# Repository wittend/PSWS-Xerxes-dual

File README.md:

# PSWS-Xerxes-dual
An SDR dual using ADC2808 converters and an FX-3 USB3 interface

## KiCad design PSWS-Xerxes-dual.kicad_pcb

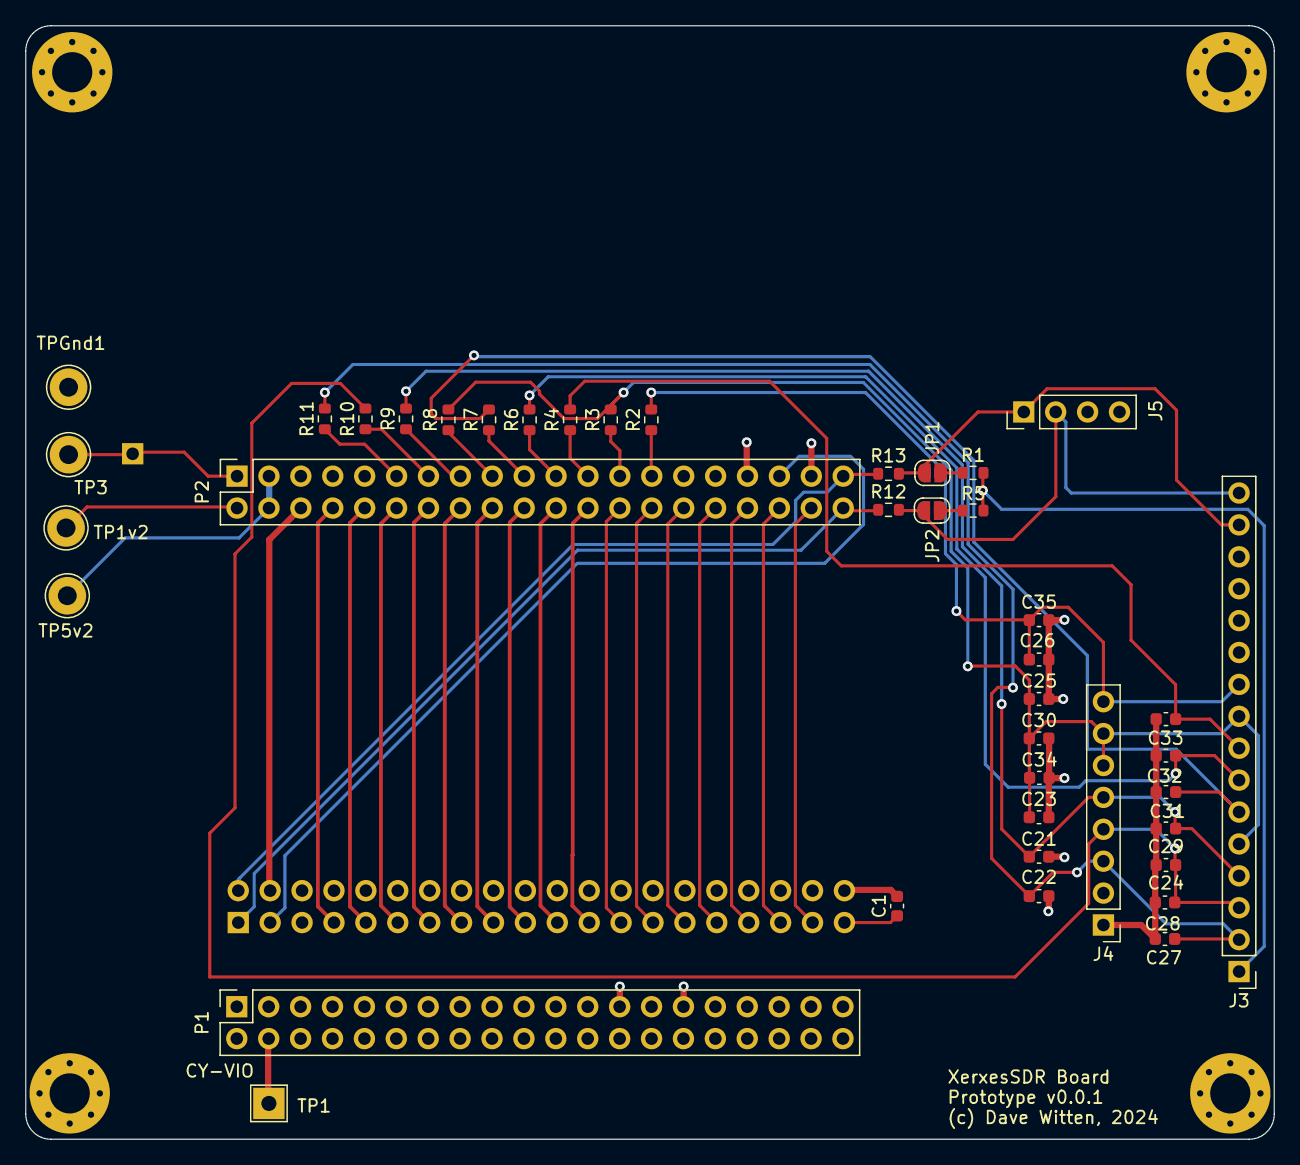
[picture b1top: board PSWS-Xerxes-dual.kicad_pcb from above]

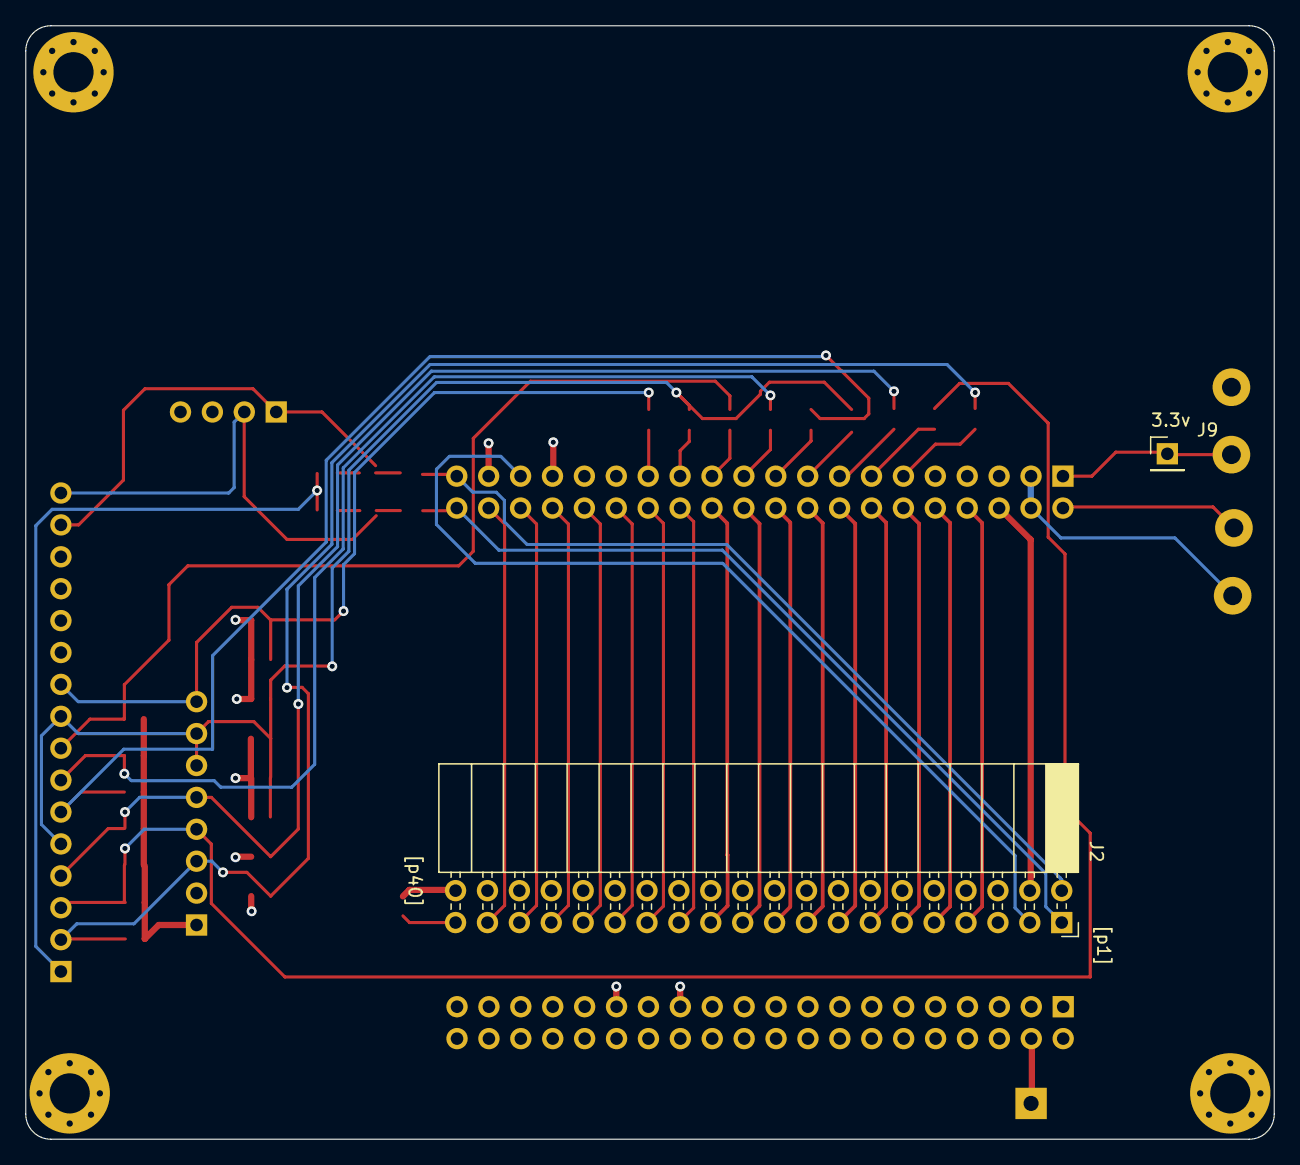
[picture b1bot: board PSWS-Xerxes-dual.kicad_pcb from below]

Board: 4 copper layers, 99.4 x 88.6 mm, 47 parts (2 on the bottom side), 46 nets.

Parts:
C1: 0.1uF; C_0603_1608Metric
C21, C22, C23, C24, C25, C26, C27, C28, C29, C30, C31, C32, C33, C34, C35: 100pf; C_0603_1608Metric
H1, H2, H3, H4: MountingHole; MountingHole_3.2mm_M3_Pad_Via
J2: 2x20-Odd/Even; PinSocket_2x20_P2.54mm_Horizontal
J3: Conn_01x16; PinHeader_1x16_P2.54mm_Vertical
J4: Conn_01x08; PinHeader_1x08_P2.54mm_Vertical
J5: Conn_01x04; PinHeader_1x04_P2.54mm_Vertical
J9: VDD (3.3v); PinHeader_1x01_P2.54mm_Vertical
JP1, JP2: Jumper_2_Open; SolderJumper-2_P1.3mm_Open_RoundedPad1.0x1.5mm
P1: J7; PinSocket_2x20_P2.54mm_Vertical
P2: J6; PinSocket_2x20_P2.54mm_Vertical
R1, R3, R5: 10k; R_0603_1608Metric
R2, R4, R6, R7, R8, R9, R10, R11: 1k; R_0603_1608Metric
R12, R13: 0; R_0603_1608Metric
TP1: TPCyVIO; TestPoint_THTPad_2.5x2.5mm_Drill1.2mm
TP1v2: TP1v2; TestPoint_THTPad_D3.0mm_Drill1.5mm
TP3: TP3v3; TestPoint_THTPad_D3.0mm_Drill1.5mm
TP5v2: TP5v; TestPoint_THTPad_D3.0mm_Drill1.5mm
TPGnd1: TPGnd; TestPoint_THTPad_D3.0mm_Drill1.5mm

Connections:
1.2v: P1.2, P2.2, TP1v2.1
3.3v: J9.1, P1.1, P2.1, TP3.1
ATT CLK: C32.1, J3.7, R6.2
ATT DATA: C31.1, J3.6, R7.2
ATT LE: C33.1, J3.8, R4.2
CyVio: P1.4, TP1.1
D0: J2.37, P2.38
D1: J2.35, P2.36
D2: J2.33, P2.34
D3: J2.31, P2.32
D4: J2.29, P2.30
D5: J2.27, P2.28
D6: J2.25, P2.26
D7: J2.23, P2.24
D8: J2.21, P2.22
D9: J2.19, P2.20
D10: J2.17, P2.18
D11: J2.15, P2.16
D12: J2.13, P2.14
D13: J2.11, P2.12
D14: J2.9, P2.10
D15: J2.7, P2.8
GND: C1.2, C21.2, C22.2, C23.2, C24.2, C25.2, C26.2, C27.2, C28.2, C29.2, C30.2, C31.2, C32.2, C33.2, C34.2, C35.2, H1.1, H2.1, H3.1, H4.1, J2.4, J2.5, J2.6, J2.8, J2.10, J2.12, J2.14, J2.16, J2.18, J2.20, J2.22, J2.24, J2.26, J2.28, J2.30, J2.32, J2.34, J2.36, J2.38, J2.40, J3.11, J3.14, J4.1, J5.4, P1.13, P1.15, P1.17, P1.25, P1.29, P1.39, P1.40, P2.5, P2.6, P2.33, P2.37, TPGnd1.1
GPIO19: P2.27, R2.1
GPIO20: P2.25, R3.1
GPIO21: P2.23, R4.1
GPIO22: P2.21, R6.1
GPIO23: P2.19, R7.1
GPIO24: P2.17, R8.1
GPIO25: P2.15, R9.1
GPIO26: P2.13, R10.1
GPIO27: P2.11, R11.1
I2C SCL: J2.1, P2.40, R12.1
I2C SDA: J2.2, P2.39, R13.1
unnamed: C1.1, J2.39
unnamed: C22.1, C27.1, J3.2, J4.3, R11.2
unnamed: C24.1, C28.1, J3.3, J4.4, R10.2
unnamed: C21.1, C29.1, J3.4, J4.5, R9.2
unnamed: C23.1, C25.1, C30.1, C34.1, J3.5, J3.9, J4.6, J4.7, R3.2, R8.2
unnamed: C26.1, C35.1, J3.10, J4.8, R2.2
unnamed: J3.15, J5.1, JP1.2 (B), R13.2
unnamed: J3.16, J5.2, JP2.2 (B), R12.2
unnamed: JP1.1 (A), R1.2
unnamed: JP2.1 (A), R5.2
PCLK: J2.3, P2.35
VBUS: J3.1, P2.3, P2.4, R1.1, R5.1, TP5v2.1

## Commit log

2025-04-29 Initial upload
